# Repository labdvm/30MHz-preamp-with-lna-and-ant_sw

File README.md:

# 30MHz-preamp-with-lna-and-ant_sw
30MHz preamp with lna and ant_sw
This module "RF-in" and "RF-out" must be attached between first capacitor and two clamping diodes like as picture "bypass.jpg".
Power supply for this module is attached to main RX-power supply for receiver.
V1.0
Z32IT

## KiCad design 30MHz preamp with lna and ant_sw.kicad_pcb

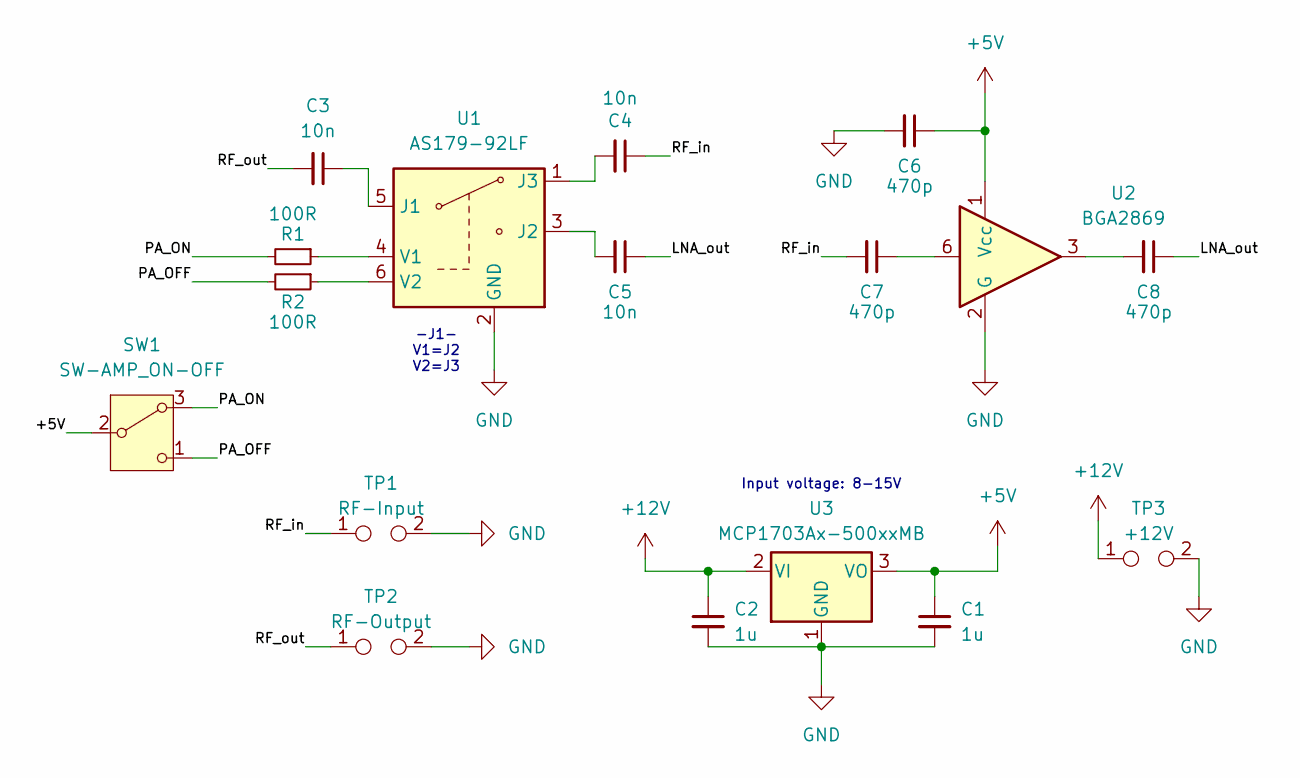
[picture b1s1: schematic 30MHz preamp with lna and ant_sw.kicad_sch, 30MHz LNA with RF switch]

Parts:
C1, C2: 1u; C_0805_2012Metric
C3, C4, C5: 10n; C_0805_2012Metric
C6, C7, C8: 470p; C_0805_2012Metric
R1, R2: 100R; R_0805_2012Metric
SW1: SW-AMP_ON-OFF; Nidec_Copal_CAS-120A
TP1: RF-Input; TestPoint_2Pads_Pitch5.08mm_Drill1.3mm
TP2: RF-Output; TestPoint_2Pads_Pitch5.08mm_Drill1.3mm
TP3: +12V; TestPoint_2Pads_Pitch5.08mm_Drill1.3mm
U1: AS179-92LF; SOT-363_SC-70-6
U2: BGA2869; SOT-363_SC-70-6
U3: MCP1703Ax-500xxMB; SOT-89-3

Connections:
+5V: C1.1, C6.1, SW1.2 (B), U2.1 (Vcc), U3.3 (VO)
+12V: C2.1, TP3.1, U3.2 (VI)
/LNA_out: C5.1, C8.1
/PA_OFF: R2.2, SW1.1 (C)
/PA_ON: R1.2, SW1.3 (A)
/RF_in: C4.1, C7.2, TP1.1
/RF_out: C3.2, TP2.1
GND: C1.2, C2.2, C6.2, TP1.2, TP2.2, TP3.2, U1.2 (GND), U2.2 (G), U2.4 (G), U2.5 (G), U3.1 (GND)
unnamed: C7.1, U2.6
unnamed: C8.2, U2.3
unnamed: C3.1, U1.5 (J1)
unnamed: C5.2, U1.3 (J2)
unnamed: C4.2, U1.1 (J3)
unnamed: R1.1, U1.4 (V1)
unnamed: R2.1, U1.6 (V2)

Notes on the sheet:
Input voltage: 8-15V
-J1- V1=J2 V2=J3

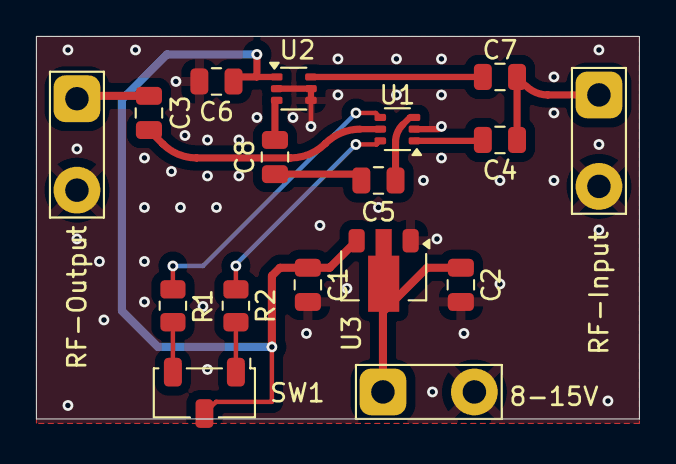
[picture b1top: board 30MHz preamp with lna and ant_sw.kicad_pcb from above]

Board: 2 copper layers, 33.5 x 21.2 mm, 17 parts (0 on the bottom side), 15 nets.
